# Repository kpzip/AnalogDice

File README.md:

# AnalogDice
fully analog electronic dice

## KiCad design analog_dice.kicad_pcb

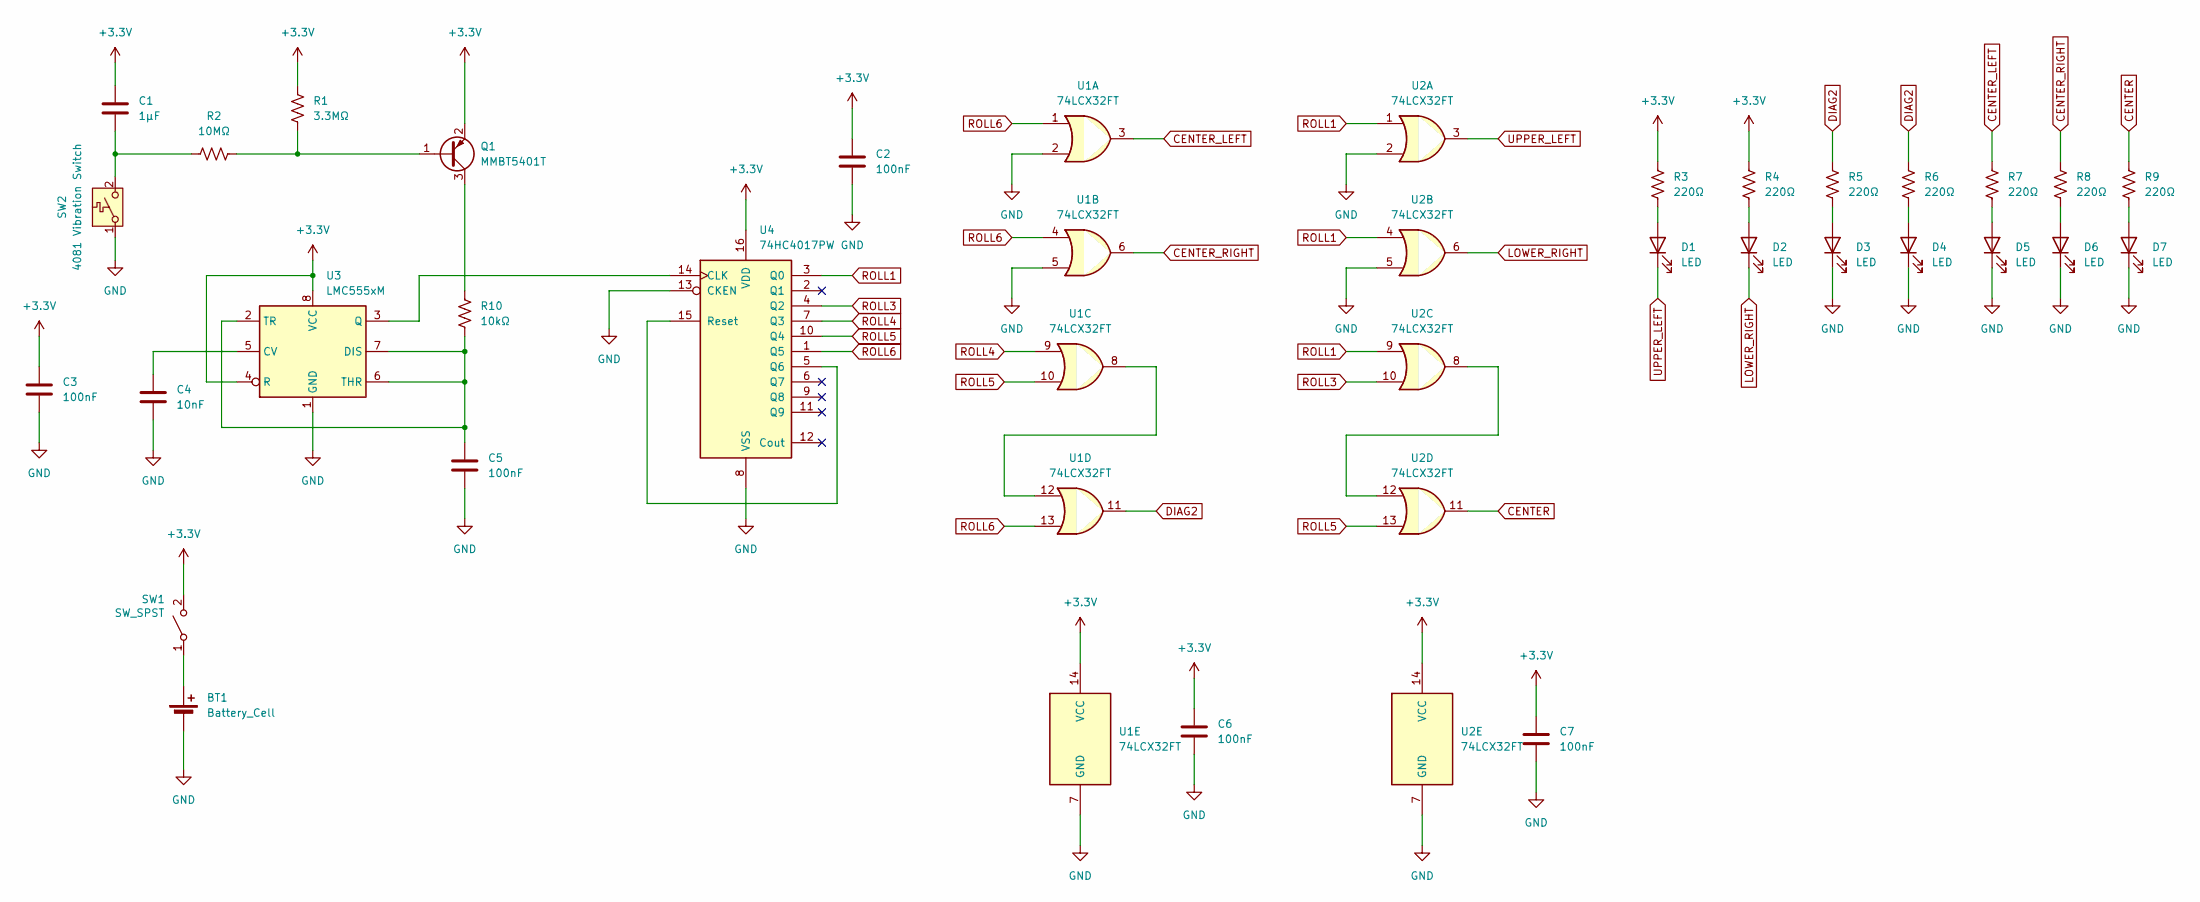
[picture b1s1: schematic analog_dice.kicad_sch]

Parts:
BT1: Battery_Cell; BAT-HLD-001; Manufacturer Part Number BAT-HLD-001
C1: 1μF; C_0201_0603Metric; Manufacturer Part Number CL03A105MQ3CSNH
C2, C3, C5, C6, C7: 100nF; C_0201_0603Metric; Manufacturer Part Number GRM033R61A104KE15D
C4: 10nF; C_0201_0603Metric; Manufacturer Part Number GRM033R71A103KA01D
D1, D2, D3, D4, D5, D6, D7: LED; LED_0805_2012Metric; Manufacturer Part Number YLED0805G
Q1: MMBT5401T; SOT-523; Manufacturer Part Number MMBT5401T
R1: 3.3MΩ; R_0201_0603Metric; Manufacturer Part Number RK73B1HTTC335J
R2: 10MΩ; R_0201_0603Metric; Manufacturer Part Number 0201WMF1005TEE
R3, R4, R5, R6, R7, R8, R9: 220Ω; R_0201_0603Metric; Manufacturer Part Number RC0201FR-07220RL
R10: 10kΩ; R_0201_0603Metric; Manufacturer Part Number RC0201FR-0710KL
SW1: SW_SPST; SW_DIP_SPSTx01_Slide_Copal_CHS-01B_W7.62mm_P1.27mm; Manufacturer Part Number CHS-01B1
SW2: 4081 Vibration Switch; 4081
U1, U2: 74LCX32FT; TSSOP-14_4.4x5mm_P0.65mm; Manufacturer Part Number 74LCX32FT
U3: LMC555xM; SOIC-8_3.9x4.9mm_P1.27mm; Manufacturer Part Number LMC555CMX/NOPB
U4: 74HC4017PW; TSSOP-16_4.4x5mm_P0.65mm; Manufacturer Part Number 74HC4017PW,118

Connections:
+3.3V: C1.1, C2.1, C3.1, C6.1, C7.1, Q1.2 (E), R1.2, R3.1, R4.1, SW1.2 (B), U1.14 (VCC), U2.14 (VCC), U3.4 (R), U3.8 (VCC), U4.16 (VDD)
CENTER: R9.1, U2.11
CENTER_LEFT: R7.1, U1.3
CENTER_RIGHT: R8.1, U1.6
DIAG2: R5.1, R6.1, U1.11
GND: BT1.2 (-), C2.2, C3.2, C4.2, C5.2, C6.2, C7.2, D3.1 (K), D4.1 (K), D5.1 (K), D6.1 (K), D7.1 (K), SW2.1 (A), U1.2, U1.5, U1.7 (GND), U2.2, U2.5, U2.7 (GND), U3.1 (GND), U4.8 (VSS), U4.13 (CKEN)
LOWER_RIGHT: D2.1 (K), U2.6
unnamed: BT1.1 (+), SW1.1 (A)
unnamed: D1.2 (A), R3.2
unnamed: D2.2 (A), R4.2
unnamed: D3.2 (A), R5.2
unnamed: D4.2 (A), R6.2
unnamed: D5.2 (A), R7.2
unnamed: D6.2 (A), R8.2
unnamed: D7.2 (A), R9.2
unnamed: Q1.1 (B), R1.1, R2.2
unnamed: Q1.3 (C), R10.1
unnamed: C1.2, R2.1, SW2.2 (B)
unnamed: U1.8, U1.12
unnamed: U2.8, U2.12
unnamed: C4.1, U3.5 (CV)
unnamed: C5.1, R10.2, U3.2 (TR), U3.6 (THR), U3.7 (DIS)
unnamed: U3.3 (Q), U4.14 (CLK)
unnamed: U4.5 (Q6), U4.15 (Reset)
ROLL1: U2.1, U2.4, U2.9, U4.3 (Q0)
ROLL3: U2.10, U4.4 (Q2)
ROLL4: U1.9, U4.7 (Q3)
ROLL5: U1.10, U2.13, U4.10 (Q4)
ROLL6: U1.1, U1.4, U1.13, U4.1 (Q5)
UPPER_LEFT: D1.1 (K), U2.3

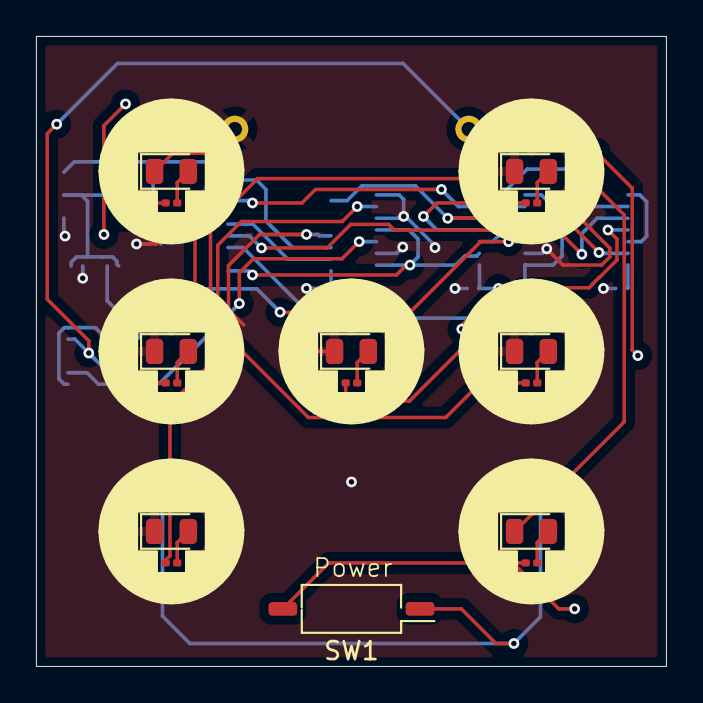
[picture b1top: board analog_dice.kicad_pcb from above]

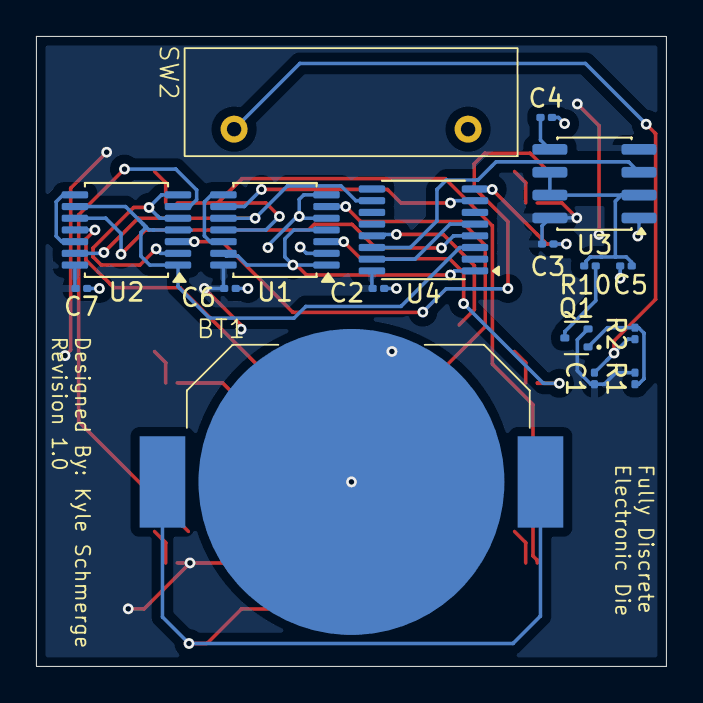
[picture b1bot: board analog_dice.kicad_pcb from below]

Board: 2 copper layers, 35.0 x 35.0 mm, 32 parts (17 on the bottom side), 30 nets.

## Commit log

2025-12-19 finish?
2025-12-19 simulate
2025-12-19 plot
